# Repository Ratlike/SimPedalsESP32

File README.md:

# SimPedalsESP32

DIY sim racing pedals using an ESP32-S3. Supports brake, accelerator, clutch, and handbrake — shows up as a USB gamepad on your PC.

## Hardware

- **ESP32-S3** microcontroller
- **Brake** — load cell + ADS1256 ADC
- **Accelerator & Clutch** — Hall-effect sensors
- **Handbrake** — load cell + HX711 ADC
- **2 buttons** for shifter / calibration

The `hardware/` folder has the KiCad PCB project and STEP files for a 3D-printed case.

## Building

Arduino IDE project targeting the ESP32-S3. Install the ESP32 board package, then add these libraries:

- [ADS1256](https://github.com/adienakhmad/ADS1256)
- [Joystick_ESP32S2](https://github.com/schnoog/Joystick_ESP32S2)
- [HX711](https://github.com/bogde/HX711)
- [Bounce2](https://github.com/thomasfredericks/Bounce2)

Open `SimPedalsESP32.ino` and upload.

## Calibration

1. Open a serial monitor at 115200 baud.
2. Hold **Button 1** for 3 seconds to enter calibration mode.
3. Press **Button 2** to cycle through pedals.
4. Leave each pedal at rest for 2 seconds, then press it to its max. The serial monitor shows the current raw value, min, and max in real time.
5. Hold **Button 1** for 3 seconds to save and exit.

Calibration is saved to flash and persists across power cycles.

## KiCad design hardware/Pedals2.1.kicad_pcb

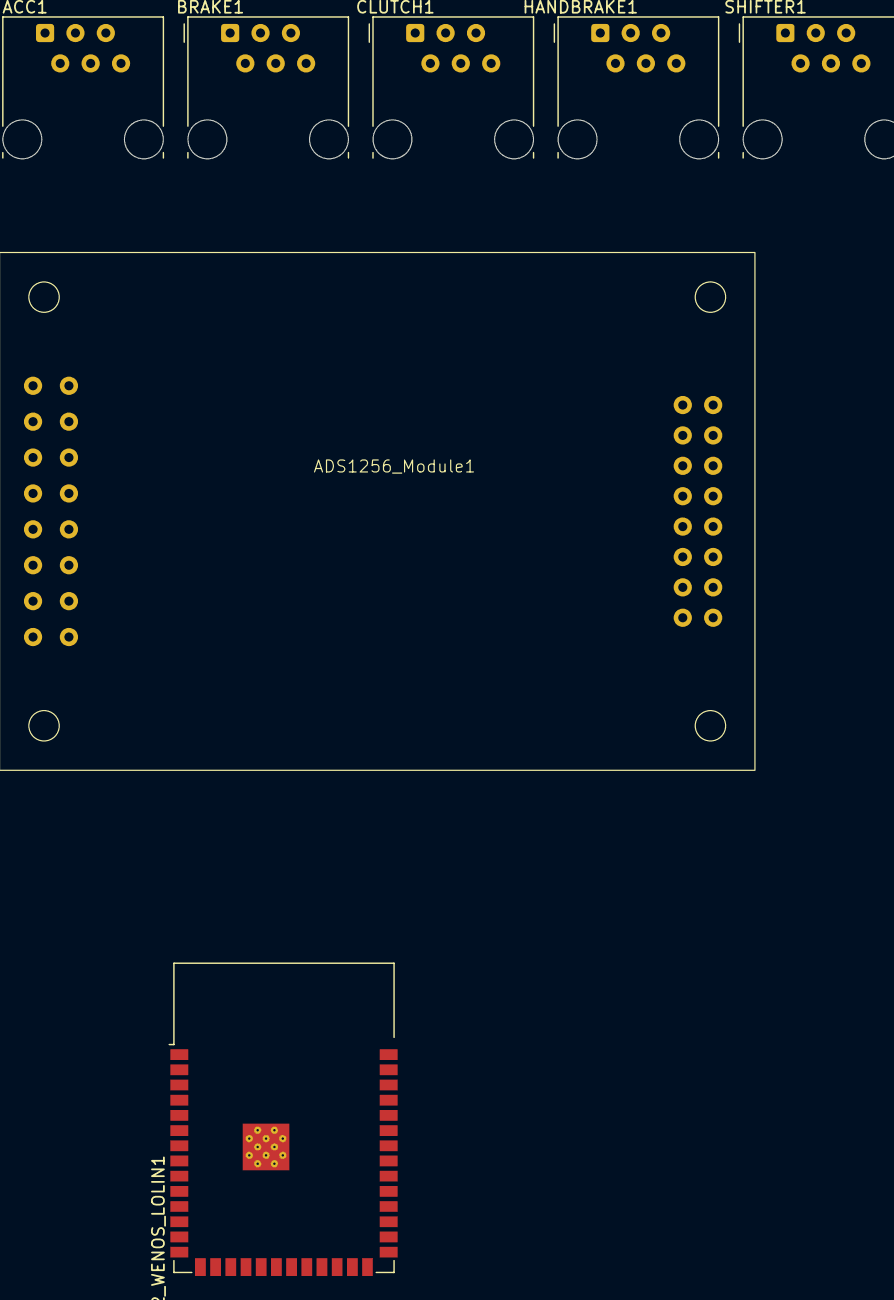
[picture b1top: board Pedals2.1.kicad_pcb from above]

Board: 2 copper layers, 7 parts (0 on the bottom side), 2 nets, no tracks yet.

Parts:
ACC1: RJ12; RJ12_Amphenol_54601-x06_Horizontal
ADS1256_Module1: ADS1256 board
BRAKE1: RJ12; RJ12_Amphenol_54601-x06_Horizontal
CLUTCH1: RJ12; RJ12_Amphenol_54601-x06_Horizontal
ESP32_WENOS_LOLIN1: ESP32-S3-WROOM-1
HANDBRAKE1: RJ12; RJ12_Amphenol_54601-x06_Horizontal
SHIFTER1: RJ12; RJ12_Amphenol_54601-x06_Horizontal

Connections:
+3V3: ACC1.1, ACC1.2, BRAKE1.1, BRAKE1.2, CLUTCH1.1, CLUTCH1.2, HANDBRAKE1.1, HANDBRAKE1.2, SHIFTER1.1, SHIFTER1.2
GND: ACC1.5, ACC1.6, BRAKE1.5, BRAKE1.6, CLUTCH1.5, CLUTCH1.6, HANDBRAKE1.5, HANDBRAKE1.6, SHIFTER1.5, SHIFTER1.6

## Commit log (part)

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2025-07-03 Add files via upload
    Initial commit.
2025-07-03 Reading ADS1256 moved to core 1
2025-07-05 Fixed broken setZeroPoint and estimateVariance.
2025-07-06 Offload Hall sensor sampling to core 1, flush S/H cap, and add EMA filtering
    - Move ACCEL_PIN_2/CLUTCH_PIN_2 reads from loop()’s analogRead() into a FreeRTOS task pinned to core 1 at 1 kHz
    - Perform a dummy ADC read before each real sample to flush the sample-and-hold capacitor and prevent crosstalk
    - Apply exponential moving average (α = 0.30) to accelerator and clutch readings for jitter reduction
2025-07-10 Improved brake pedal responsiveness. Fixed brake zero point calculation not executing.
2026-02-26 Intitial commit
2026-02-26 Hardware project files added
2026-02-26 STEP files for case
2026-02-26 Image of finished device
2026-02-27 Dynamic rezero of pedals
2026-02-27 Autozero enabled flag
